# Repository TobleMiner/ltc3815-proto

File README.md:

LTC3815 proto board
===================

A simple prototyping board for the LTC3815 digitally programmable buck regulator

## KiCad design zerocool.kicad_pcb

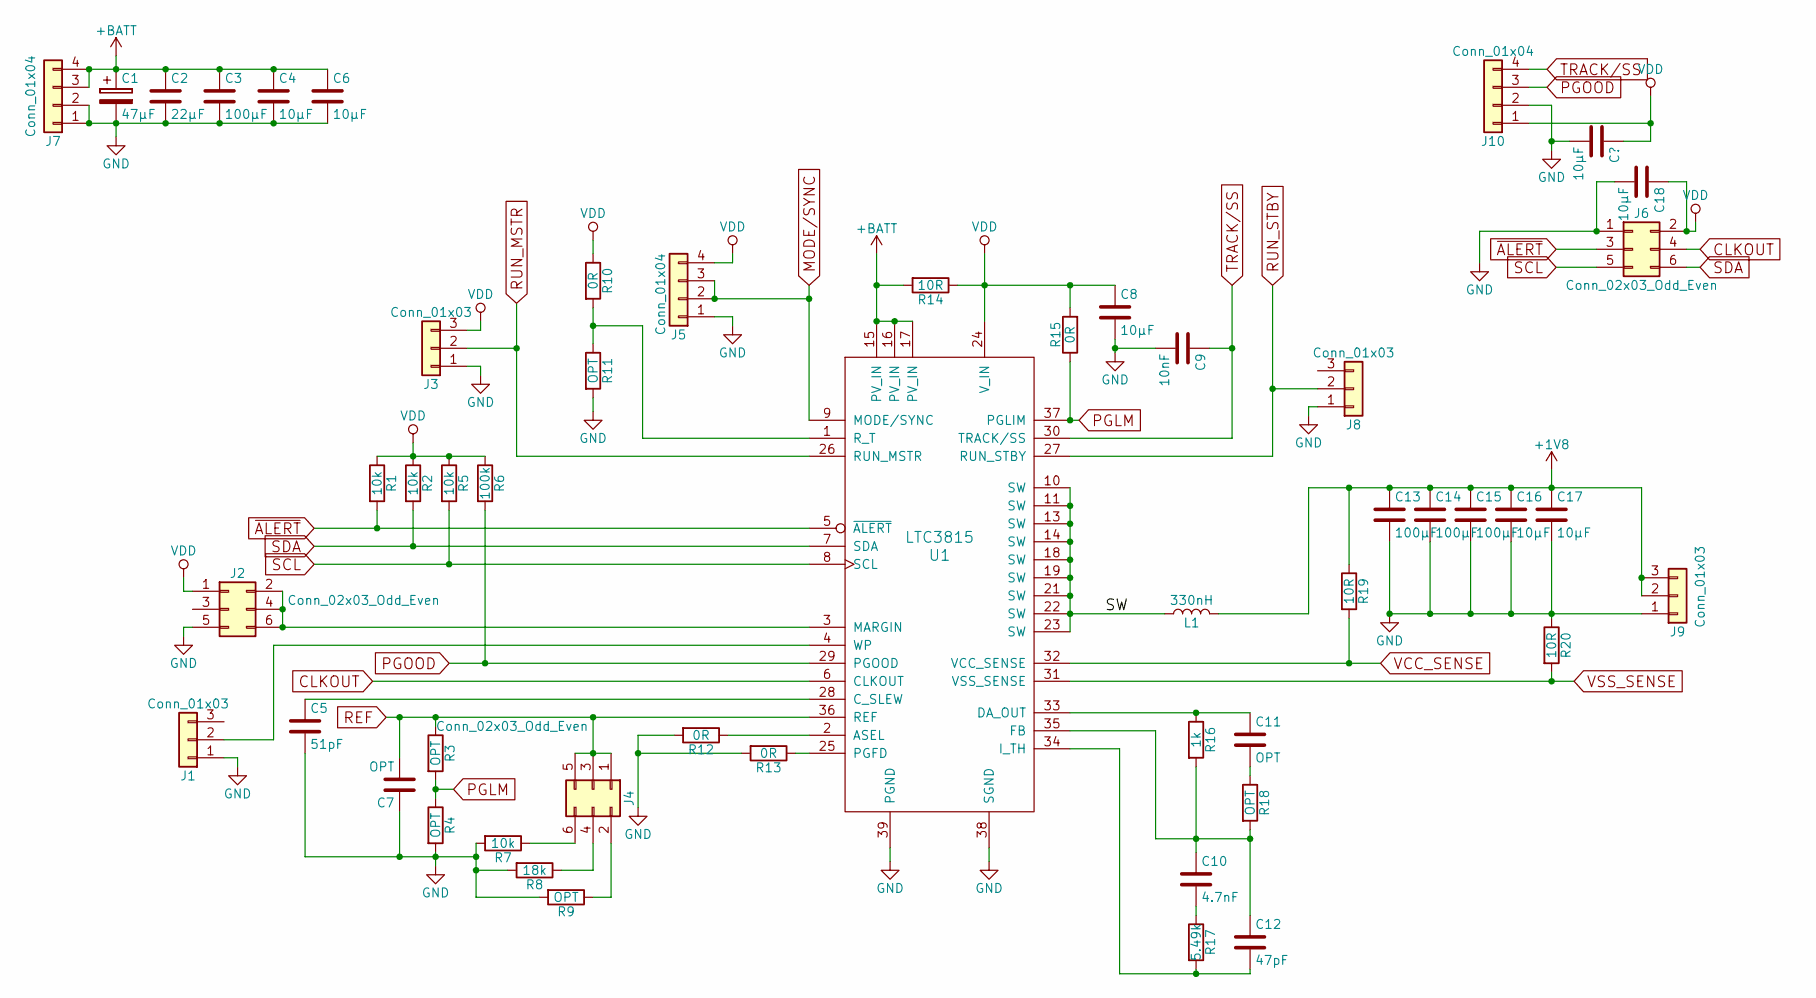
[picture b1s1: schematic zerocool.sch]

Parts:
C1: 47µF; CP_Poly_Panasonic_C6
C2: 22µF; C_1206_HandSoldering
C3, C13, C14, C15: 100µF; C_1210_HandSoldering
C4, C6, C8, C16, C17: 10µF; C_1206_HandSoldering
C5: 51pF; C_0805
C7: OPT; C_0805_HandSoldering
C9: 10nF; C_0805
C10: 4.7nF; C_0805
C11: OPT; C_0805
C12: 47pF; C_0805
C18: 10µF; C_0805_HandSoldering
J1, J3, J8, J9: Conn_01x03; Pin_Header_Straight_1x03_Pitch2.54mm
J2, J4, J6: Conn_02x03_Odd_Even; Pin_Header_Straight_2x03_Pitch2.54mm
J5, J7, J10: Conn_01x04; Pin_Header_Straight_1x04_Pitch2.54mm
L1: 330nH; Coilcraft_XAL60XX
R1, R2, R5, R7: 10k; R_0805
R3, R4, R9, R11, R18: OPT; R_0805
R6: 100k; R_0805
R8: 18k; R_0805
R10, R12, R13, R15: 0R; R_0805
R14: 10R; R_1206
R16: 1k; R_0805
R17: 5.49k; R_0805
R19, R20: 10R; R_0805
U1: LTC3815; QFN-38-1EP_4x6mm_Pitch0.4mm

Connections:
+1V8: C13.1, C14.1, C15.1, C16.1, C17.1, J9.2, J9.3, L1.2, R19.1
+BATT: C1.1, C2.1, C3.1, C4.1, C6.1, J7.3, J7.4, R14.2, U1.15 (PV_IN), U1.16 (PV_IN), U1.17 (PV_IN)
/SW: L1.1, U1.10 (SW), U1.11 (SW), U1.13 (SW), U1.14 (SW), U1.18 (SW), U1.19 (SW), U1.21 (SW), U1.22 (SW), U1.23 (SW)
CLKOUT: J6.4, U1.6 (CLKOUT)
GND: C1.2, C2.2, C3.2, C4.2, C5.2, C6.2, C7.1, C8.2, C9.2, C13.2, C14.2, C15.2, C16.2, C17.2, C18.2, J1.1, J2.5, J3.1, J5.1, J6.1, J7.1, J7.2, J8.1, J9.1, J10.2, R4.2, R7.2, R8.2, R9.2, R11.2, R12.2, R13.2, R20.1, U1.38 (SGND), U1.39 (PGND); also elsewhere on the board
MODE/SYNC: J5.2, J5.3, U1.9 (MODE/SYNC)
unnamed: C5.1, U1.28 (C_SLEW)
unnamed: C10.1, C12.1, R16.2, R18.2, U1.35 (FB)
unnamed: C10.2, R17.1
unnamed: C11.1, R16.1, U1.33 (DA_OUT)
unnamed: C11.2, R18.1
unnamed: C12.2, R17.2, U1.34 (I_TH)
unnamed: J1.2, U1.4 (WP)
unnamed: J2.2, J2.4, J2.6, U1.3 (MARGIN)
unnamed: J4.2, R9.1
unnamed: J4.4, R8.1
unnamed: J4.6, R7.1
unnamed: R10.2, R11.1, U1.1 (R_T)
unnamed: R12.1, U1.2 (ASEL)
unnamed: R13.1, U1.25 (PGFD)
PGLM: R3.2, R4.1, R15.1, U1.37 (PGLIM)
PGOOD: J10.3, R6.2, U1.29 (PGOOD)
REF: C7.2, J4.1, J4.3, J4.5, R3.1, U1.36 (REF)
RUN_MSTR: J3.2, U1.26 (RUN_MSTR)
RUN_STBY: J8.2, U1.27 (RUN_STBY)
SCL: J6.5, R5.2, U1.8 (SCL)
SDA: J6.6, R2.2, U1.7 (SDA)
TRACK/SS: C9.1, J10.4, U1.30 (TRACK/SS)
VCC_SENSE: R19.2, U1.32 (VCC_SENSE)
VDD: C8.1, C18.1, J2.1, J3.3, J5.4, J6.2, J10.1, R1.1, R2.1, R5.1, R6.1, R10.1, R14.1, R15.2, U1.24 (V_IN); also elsewhere on the board
VSS_SENSE: R20.2, U1.31 (VSS_SENSE)
~ALERT: J6.3, R1.2, U1.5 (~ALERT)

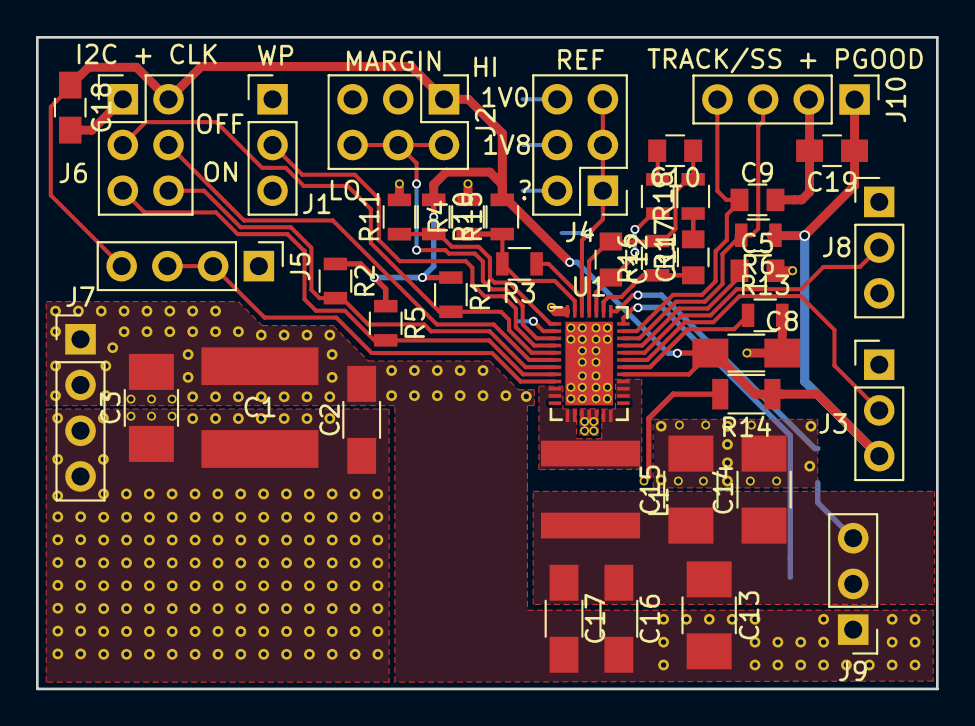
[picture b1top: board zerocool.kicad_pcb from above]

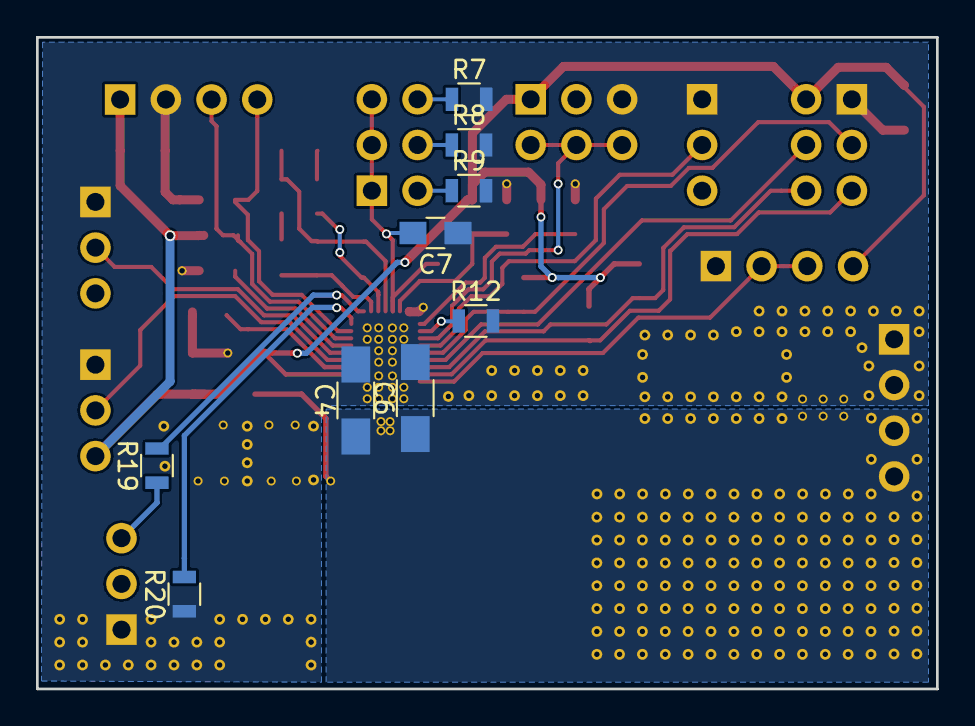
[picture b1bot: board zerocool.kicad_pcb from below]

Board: 2 copper layers, 50.0 x 36.2 mm, 51 parts (9 on the bottom side), 32 nets.

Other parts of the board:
C19: 10µF; C_0805_HandSoldering

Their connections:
GND: C19.2; also elsewhere on the board
VDD: C19.1; also elsewhere on the board

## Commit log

2017-11-19 Add additional via stitching on ground plane
2017-11-22 Add small readme
2017-11-22 Add pcb screenshot
2017-11-22 Add screenshot to README
